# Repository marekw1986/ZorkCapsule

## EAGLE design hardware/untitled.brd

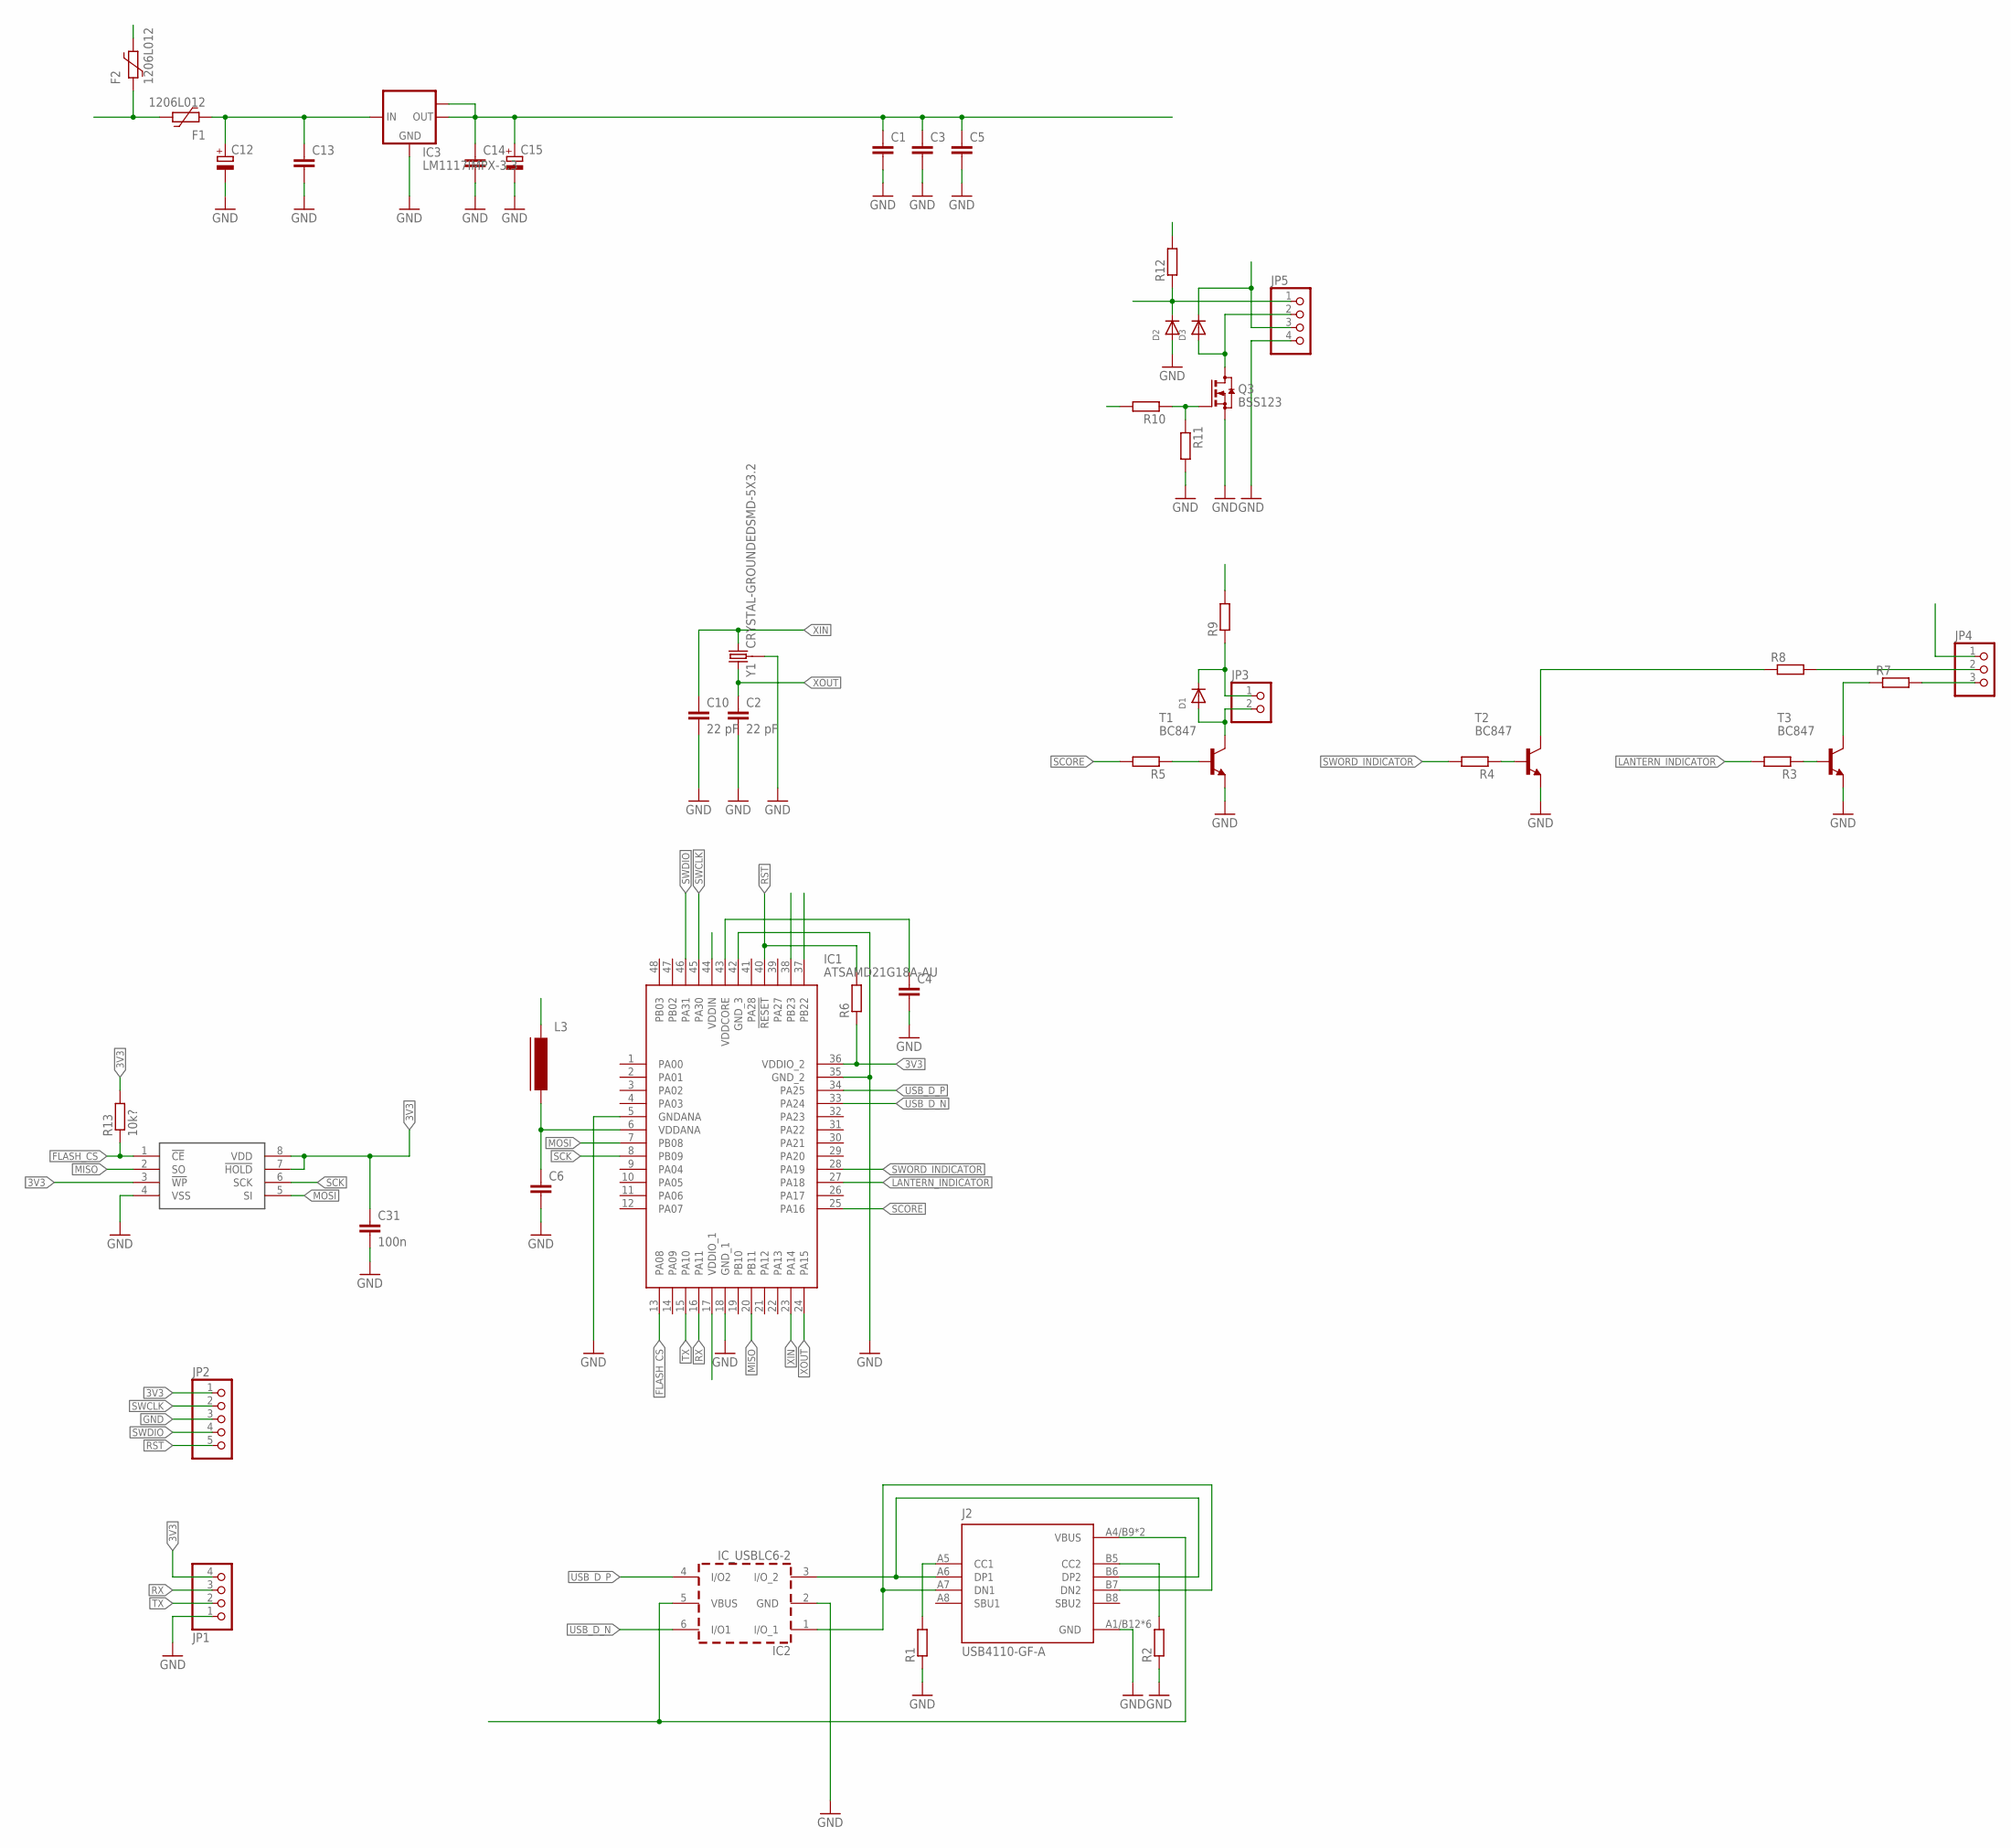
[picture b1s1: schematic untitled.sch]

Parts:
C1, C3, C4, C5, C6: C-EUC0402; C0402
C2, C10: 22 pF; C0603
C12, C15: CPOL-EUSMCB; SMC_B
C13, C14: C-EUC0603; C0603
C31: 100n; C0603
D1, D2, D3: DIODESOD-323; SOD-323
F1, F2: 1206L012; 1206L
IC1: ATSAMD21G18A-AU; QFP50P900X900X120-48N
IC2: IC_USBLC6-2; SOT-23-6L
IC3: LM1117IMPX-3.3; SOT223
J2: USB4110-GF-A; GCT_USB4110-GF-A
JP1, JP5: PINHD-1X4; 1X04
JP2: PINHD-1X5; 1X05
JP3: PINHD-1X2; 1X02
JP4: PINHD-1X3; 1X03
L3: FERRITE-0805; FB805
Q3: BSS123; SOT23
R1, R2, R6, R9, R11, R12: R-EU_R0603; R0603
R3, R4, R5, R7, R8, R10: R-EU_R0402; R0402
R13: 10k?; R0603
T1, T2, T3: BC847; SOT23
U$2: SST25VF016BSO8M; SO-08M
Y1: CRYSTAL-GROUNDEDSMD-5X3.2; CRYSTAL-SMD-5X3.2-4PAD

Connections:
3V3: C1.1, C3.1, C5.1, C14.1, C15.+, C31.1, IC1.17 (VDDIO_1), IC1.36 (VDDIO_2), IC1.44 (VDDIN), IC3.2 (OUT), IC3.TAB (OUT1), JP1.4, JP2.1, JP4.1, L3.1, R6.1, R9.2, R12.2, R13.2, U$2.3 (!WP), U$2.7 (!HOLD), U$2.8 (VDD)
5V: C12.+, C13.1, F1.2, IC3.3 (IN)
!RST: IC1.40 (!RESET), JP2.5, R6.2
D2_N: IC2.1 (I/O_1), J2.A7 (DN1), J2.B7 (DN2)
D2_P: IC2.3 (I/O_2), J2.A6 (DP1), J2.B6 (DP2)
FLASH_CS: IC1.13 (PA08), R13.1, U$2.1 (!CE)
GND: C1.2, C2.2, C3.2, C4.2, C5.2, C6.2, C10.2, C12.-, C13.2, C14.2, C15.-, C31.2, D2.A, IC1.5 (GNDANA), IC1.18 (GND_1), IC1.35 (GND_2), IC1.42 (GND_3), IC2.2 (GND), IC3.1 (GND), J2.A1/B12 (GND), J2.B1/A12 (GND), J2.S1 (GND), J2.S2 (GND), J2.S3 (GND), J2.S4 (GND), JP1.1, JP2.3, JP5.4, Q3.2 (S), R1.1, R2.1, R11.2, T1.2 (E), T2.2 (E), T3.2 (E), U$2.4 (VSS), Y1.2 (3), Y1.4 (3)
LANTERN_INDICATOR: IC1.27 (PA18), R3.2
LOCK: IC1.37 (PB22), R10.2
LOCK_5V: D3.C, F2.1, JP5.3
LOCK_OPEN: D2.C, IC1.38 (PB23), JP5.1, R12.1
MISO: IC1.20 (PB11), U$2.2 (SO)
MOSI: IC1.7 (PB08), U$2.5 (SI)
unnamed: J2.B5 (CC2), R2.2
unnamed: J2.A5 (CC1), R1.2
unnamed: R5.1, T1.1 (B)
unnamed: D1.A, JP3.2, T1.3 (C)
unnamed: R4.1, T2.1 (B)
unnamed: R3.1, T3.1 (B)
unnamed: JP4.3, R7.2
unnamed: R7.1, T3.3 (C)
unnamed: JP4.2, R8.2
unnamed: R8.1, T2.3 (C)
unnamed: C6.1, IC1.6 (VDDANA), L3.2
unnamed: Q3.1 (G), R10.1, R11.1
unnamed: D3.A, JP5.2, Q3.3 (D)
RX: IC1.16 (PA11), JP1.3
SC3V3: D1.C, JP3.1, R9.1
SCK: IC1.8 (PB09), U$2.6 (SCK)
SCORE: IC1.25 (PA16), R5.2
SWCLK: IC1.45 (PA30), JP2.2
SWDIO: IC1.46 (PA31), JP2.4
SWORD_INDICATOR: IC1.28 (PA19), R4.2
TX: IC1.15 (PA10), JP1.2
USB_D_N: IC1.33 (PA24), IC2.6 (I/O1)
USB_D_P: IC1.34 (PA25), IC2.4 (I/O2)
VBUS: F1.1, F2.2, IC2.5 (VBUS), J2.A4/B9 (VBUS), J2.B4/A9 (VBUS)
VDDCORE: C4.1, IC1.43 (VDDCORE)
XIN: C10.1, IC1.23 (PA14), Y1.1 (2)
XOUT: C2.1, IC1.24 (PA15), Y1.3 (1)

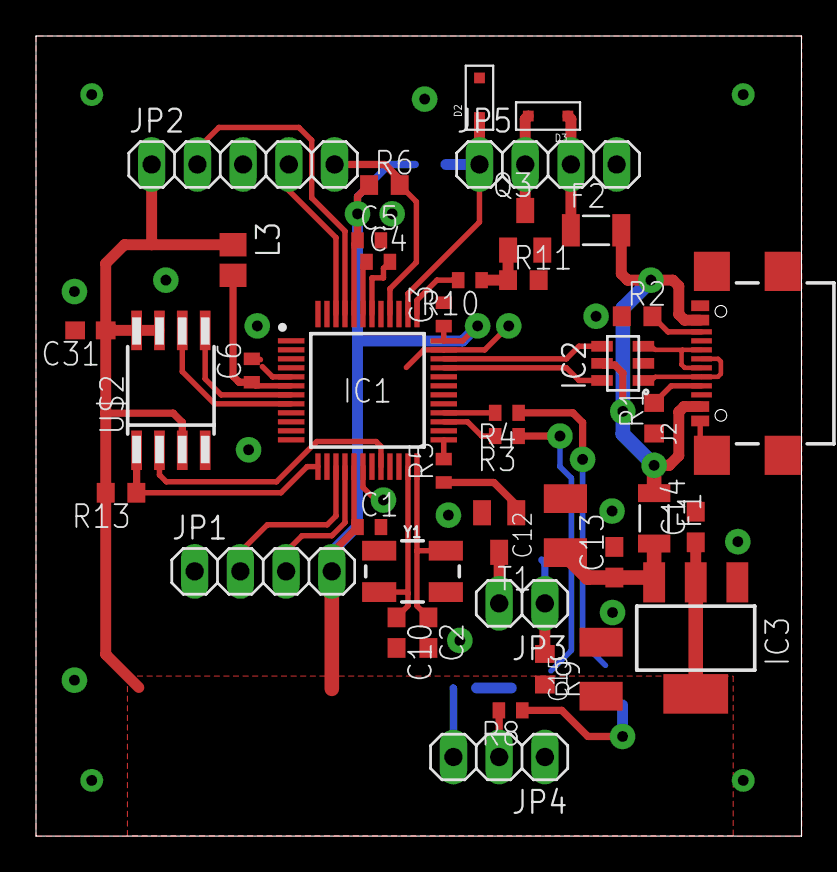
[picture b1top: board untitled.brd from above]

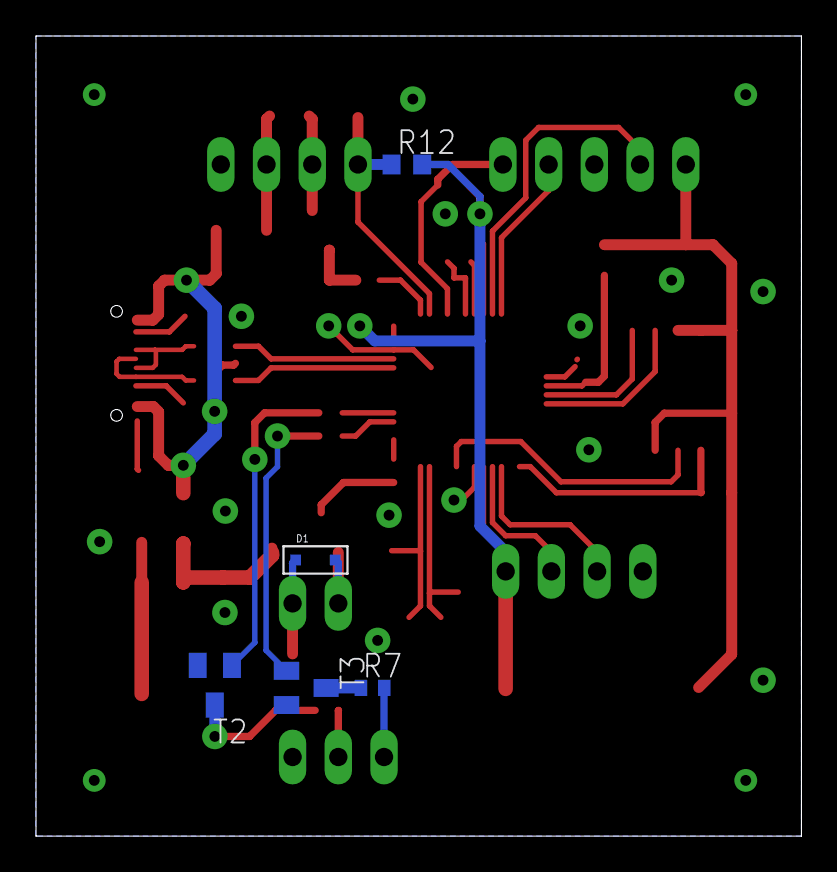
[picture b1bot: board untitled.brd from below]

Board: 2 copper layers, 42.5 x 44.5 mm, 46 parts (5 on the bottom side), 40 nets.

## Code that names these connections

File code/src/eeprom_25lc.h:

/*
 * eeprom_25lc.h
 *
 * Driver for the Microchip 25LC256 SPI EEPROM (32768 bytes, 64-byte
 * page) on ATSAMD21 via ASF3's spi_master (SERCOM SPI) driver.
 *
 * Same public interface (eeprom_status_t / eeprom_write / eeprom_read)
 * as eeprom_24lc.h, so eeprom_slots.c works unmodified against either
 * driver -- just swap which of the two headers it includes.
 */

#ifndef EEPROM_25LC_H
#define EEPROM_25LC_H

#include <stdint.h>
#include <stdbool.h>
#include <port.h>
#include <spi.h>

/* ---- Chip geometry ---- */
#define EEPROM_TOTAL_SIZE     32768u   /* 25LC256 = 32768 bytes */
#define EEPROM_PAGE_SIZE      64u

/* Chip-select pin -- set this to whatever pin you've wired CS to. */
#define EEPROM_CS_PIN         PIN_PA08

/* SERCOM instance and SPI signal routing for this board's wiring:
 *   MOSI = PB08 (SERCOM4 PAD0)
 *   SCK  = PB09 (SERCOM4 PAD1)
 *   MISO = PB11 (SERCOM4 PAD3)
 *   PAD2 (PB10, the hardware SS line) is left unused -- CS is done
 *   manually on PA08 instead, which is what EEPROM_CS_PIN is for. */
#define EEPROM_SERCOM         SERCOM4
#define EEPROM_SPI_MUX        SPI_SIGNAL_MUX_SETTING_D  /* DOPO=0 (DO=PAD0,SCK=PAD1), DIPO=3 (MISO=PAD3) */
#define EEPROM_PINMUX_PAD0    PINMUX_PB08D_SERCOM4_PAD0  /* MOSI */
#define EEPROM_PINMUX_PAD1    PINMUX_PB09D_SERCOM4_PAD1  /* SCK  */
#define EEPROM_PINMUX_PAD2    PINMUX_UNUSED              /* unused (manual CS instead) */
#define EEPROM_PINMUX_PAD3    PINMUX_PB11D_SERCOM4_PAD3  /* MISO */

/* 25LC256 instruction set */
#define EEPROM_CMD_READ   0x03u
#define EEPROM_CMD_WRITE  0x02u
#define EEPROM_CMD_WRDI   0x04u  /* write disable */
#define EEPROM_CMD_WREN   0x06u  /* write enable -- must precede every write */
#define EEPROM_CMD_RDSR   0x05u  /* read status register */
#define EEPROM_CMD_WRSR   0x01u  /* write status register */
#define EEPROM_SR_WIP     0x01u  /* write-in-progress bit in status register */

typedef enum {
    EEPROM_OK = 0,
    EEPROM_ERR_BUS,
    EEPROM_ERR_TIMEOUT,
    EEPROM_ERR_RANGE
} eeprom_status_t;

/* Call once at startup. Owns its own spi_module instance internally,
 * configures SERCOM4 per EEPROM_SERCOM/EEPROM_SPI_MUX/EEPROM_PINMUX_*
 * above, sets up the manual CS pin, and enables the peripheral --
 * nothing else needs to be done by the caller first. */
void eeprom_hw_init(void);

/* Page-boundary-safe write with WREN + status-register polling for
 * write-cycle completion. Blocking. */
eeprom_status_t eeprom_write(uint16_t addr, const uint8_t *data, uint16_t len);

/* Sequential read. Blocking. */
eeprom_status_t eeprom_read(uint16_t addr, uint8_t *data, uint16_t len);

#endif /* EEPROM_25LC_H */

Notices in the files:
parts and their libraries:
SparkFun-Clocks: Licensing: Creative Commons ShareAlike 4.0 International - https://creativecommons.org/licenses/by-sa/4.0
